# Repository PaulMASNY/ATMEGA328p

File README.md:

Simple and cheap 8-bit development board.

### ATMEGA 328p TESTING BOARD

##### INTRO

##### SOLUTION WITH 2x16 LCD IN 4-bit MODE

    - hardware BOM
    - AVR C libraries

##### DESIGN

    - electrical schematics
    - PCB layout
    - 3D export
    
##### CONCLUSION

---------------------------------------------------------------------------------------------

##### INTRO

This project ends up with a small 8-bit micro-controller 
board, serving for testing purposes with various crystals and 
configurations. Both 3.3V and 5V power sources can be used. 

##### SOLUTION WITH 2x16 LCD IN 4-bit MODE

As an LCD to start with I have used the simplest 2x16 product, embedding the HD4478 controller. 

    - hardware BOM

The following list, generated from eagle does not contain the 2x16 LCD and 
    28 pin 0.3" DIP socket for the atmega 328p:

    - AVR C libraries

I recommend a homebrew version made from the Peter's Fleury's stub. It can be found in the folder above.

##### DESIGN

I have also privileged one-side board variant with some airwires on the high side. In fact, 
these ones can be easily done by homemade etching. As a remark to the assembly below, 
the JP3 pin is used for LCD backlight only. Both 2x16 and 4x20 LCD's fit to the 
onboard socket.

    - electrical schematics

         - PCB layout with components and wiring

Everything enters on a 70 x 100 mm one-sided PCB.

         - PCB layout for homemade etching 

The image can be copied as is and printed to transfer paper for ironing. This is the copper
side of a simple one-sided PCB.

         - 3D export

A final assembly of the protoboard is here :

A true 3D view is accessible when clicking on this link :<a href="https://autode.sk/2KtyNpq" target="_blank"> Autodesk_3D_view </a>

##### CONCLUSION

This very simple board can be made, using Chinese components, for less than 100 Rands.

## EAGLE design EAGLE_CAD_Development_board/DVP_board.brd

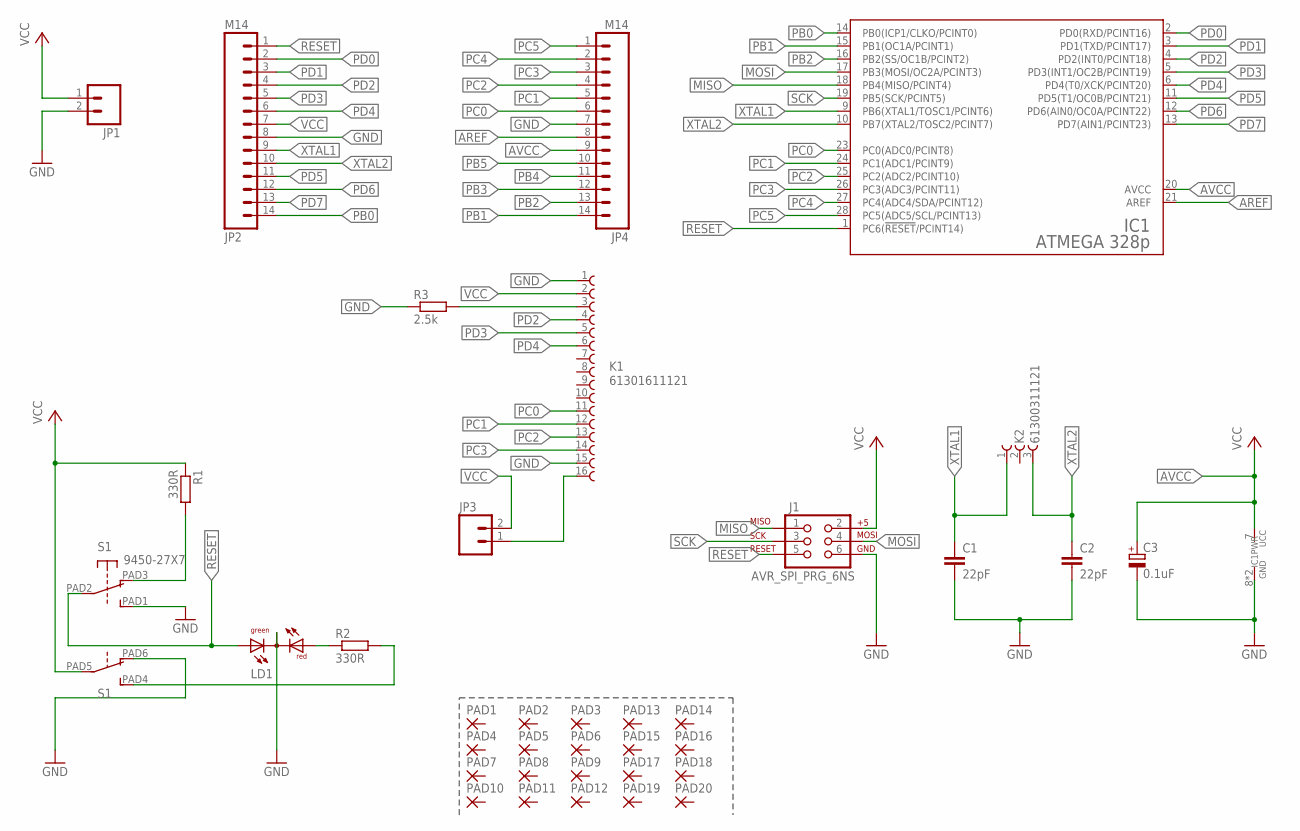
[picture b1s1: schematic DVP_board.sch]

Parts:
C1, C2: 22pF; CAP-PTH-5MM
C3: 0.1uF; E2-4
IC1: ATMEGA 328p; DIL28-3
J1: AVR_SPI_PRG_6NS; 2X3-NS
JP1: M025MM; SCREWTERMINAL-5MM-2
JP2, JP4: M14; 1X14
JP3: M02PTH; 1X02
K1: 61301611121
K2: 61300311121
LD1: DUOLED-RG-C; DUOLED-C-5MM
PAD1, PAD2, PAD3, PAD4, PAD5, PAD6, PAD7, PAD8, PAD9, PAD10, PAD11, PAD12, PAD13, PAD14, PAD15, PAD16, PAD17, PAD18, PAD19, PAD20: 1,6/0,8
R1, R2: 330R; 0207/10
R3: 2.5k; 0207/10
S1: 9450-27X7; DPDT_7X7

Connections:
AREF: IC1.21 (AREF), JP4.8
AVCC: C3.+, IC1.7 (UCC), IC1.20 (AVCC), JP4.9
GND: C1.2, C2.2, C3.-, IC1.8 (GND), IC1.22 (GND), J1.6, JP1.2, JP2.8, JP4.7, K1.1, K1.3, K1.15, LD1.C, R3.1, R3.2, S1.PAD1 (S), S1.PAD6 (O)
MISO: IC1.18 (PB4(MISO/PCINT4)), J1.1
MOSI: IC1.17 (PB3(MOSI/OC2A/PCINT3)), J1.4
unnamed: R1.2, S1.PAD3 (O)
unnamed: LD1.AR, R2.1
unnamed: R2.2, S1.PAD4 (S)
PB0: IC1.14 (PB0(ICP1/CLKO/PCINT0)), JP2.14
PB1: IC1.15 (PB1(OC1A/PCINT1)), JP4.14
PB2: IC1.16 (PB2(SS/OC1B/PCINT2)), JP4.13
PB3: JP4.12
PB4: JP4.11
PB5: JP4.10
PC0: IC1.23 (PC0(ADC0/PCINT8)), JP4.6, K1.11
PC1: IC1.24 (PC1(ADC1/PCINT9)), JP4.5, K1.12
PC2: IC1.25 (PC2(ADC2/PCINT10)), JP4.4, K1.13
PC3: IC1.26 (PC3(ADC3/PCINT11)), JP4.3, K1.14
PC4: IC1.27 (PC4(ADC4/SDA/PCINT12)), JP4.2
PC5: IC1.28 (PC5(ADC5/SCL/PCINT13)), JP4.1
PD0: IC1.2 (PD0(RXD/PCINT16)), JP2.2
PD1: IC1.3 (PD1(TXD/PCINT17)), JP2.3
PD2: IC1.4 (PD2(INT0/PCINT18)), JP2.4, K1.4
PD3: IC1.5 (PD3(INT1/OC2B/PCINT19)), JP2.5, K1.5
PD4: IC1.6 (PD4(T0/XCK/PCINT20)), JP2.6, K1.6
PD5: IC1.11 (PD5(T1/OC0B/PCINT21)), JP2.11
PD6: IC1.12 (PD6(AIN0/OC0A/PCINT22)), JP2.12
PD7: IC1.13 (PD7(AIN1/PCINT23)), JP2.13
RESET: IC1.1 (PC6(!RESET!/PCINT14)), J1.5, JP2.1, LD1.AX (AG), S1.PAD2
SCK: IC1.19 (PB5(SCK/PCINT5)), J1.3
VCC: J1.2, JP1.1, JP2.7, JP3.1, JP3.2, K1.2, K1.16, R1.1, S1.PAD5
XTAL1: C1.1, IC1.9 (PB6(XTAL1/TOSC1/PCINT6)), JP2.9, K2.1
XTAL2: C2.1, IC1.10 (PB7(XTAL2/TOSC2/PCINT7)), JP2.10, K2.3

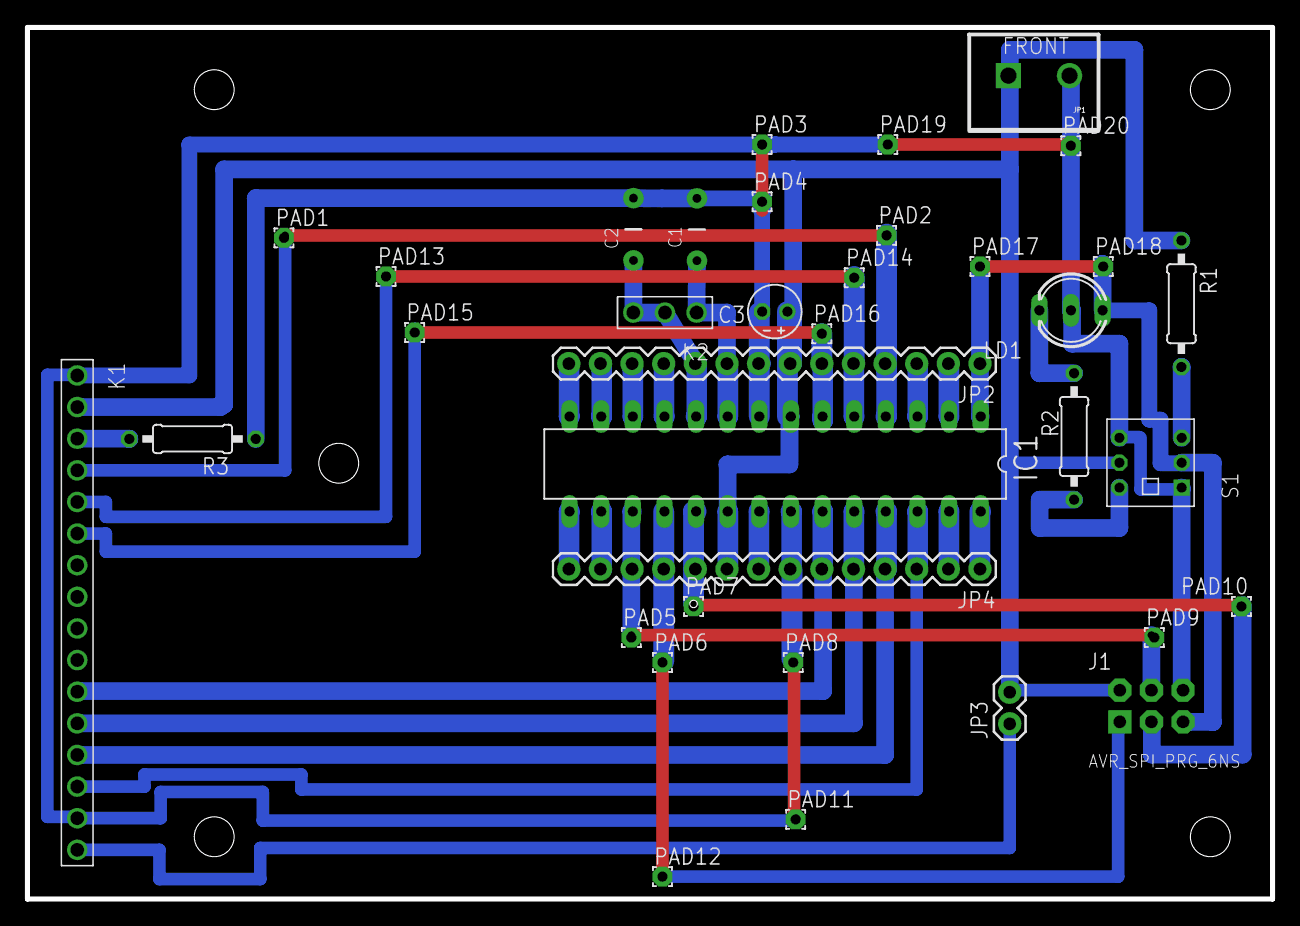
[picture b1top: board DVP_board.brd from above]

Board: 2 copper layers, 100.0 x 70.0 mm, 36 parts (0 on the bottom side), 30 nets.

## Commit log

2017-06-15 initial version
2017-06-16 # WARNING: head commit changed in the meantime
    t1.
2017-06-16 On empty file
2017-06-16 Renewal
2017-06-16 With images
2017-06-16 Image change
2017-06-20 -correction 1
2017-06-21 With toggling
2017-11-25 25th of November 2017
2018-02-04 Done
2018-02-04 Model
2018-02-04 Eagle and AUTOCAD
2018-02-04 Autodesk Link added
2018-02-04 newtab
2018-02-10 Final
2018-03-15 3D Link updated
2018-05-09 3D LInk renewed
2018-07-04 Link_Update

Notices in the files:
parts and their libraries:
SparkFun: Licensing: CC v3.0 Share-Alike You are welcome to use this library for commercial purposes.
Wurth_Elektronik_Electromechanic_Board_t: Copyright: Würth Elektronik
